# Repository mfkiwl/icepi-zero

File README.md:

# Icepi Zero - The portable FPGA development board. 

## What is the Icepi Zero?

Icepi Zero is an economical FPGA development board with a Raspberry Pi Zero form factor. It carries a Lattice ECP5 25F, enabling powerful designs while keeping a small portable size. It also has a HDMI port allowing easy digital video output.

[View PCB online](https://kicanvas.org/?github=https%3A%2F%2Fgithub.com%2Fcheyao%2Ficepi-zero%2Ftree%2Fmain%2Fhardware%2Fv1.1)

## Why Icepi Zero?

Currently most powerful FPGA boards on the market are expensive and bulky.

I've always wanted a low-cost portable FPGA with video output to make my own CPU, but there isn't any on the market.

The Icepi Zero aims to fix this. Carrying a powerful ECP5 FPGA on a small Raspberry Pi Zero form factor, it is the ultimate portable solution for FPGA development. Additionally packing a HDMI mini port and 3 USB-C ports, it allows interfacing with multiple external I/O devices.

Icepi Zero is for everyone: Students can use it to learn about the internals of modern processors. Gamers can use it to emulate old hardware. Programmers can use it to test their code on multiple architecturs.

Icepi Zero also has an on-board USB to JTAG converter, so no external programmers are needed. Moreover Icepi Zero is fully open-source, no strings attached. Fabricate your own boards if you want one!

## Features

- Raspberry Pi Zero form factor
- Lattice ECP5U FPGA:
    - 24k LUT
    - 112 KiB of RAM
- One MiniGPDI connector (it's HDM- but I don't have the money to buy a license...)
- Three USB-C Ports
- 256MiB 166MHz SDRAM
- MicroSD card slot
- On-board USB to JTAG and UART converter
- 40MHz external oscillator
- 128 Mbit of flash
- 4 user LEDs
- 1 user button

This powerful configuration allows the PCB to be used in numerous ways, including real time video processing, hardware AI acceleration and prototyping of ASICs.

## Usage

Check out the `firmware` folder for example code and compilation instructions!

## Contact

If there is any questions DM `@Cyao` on Hackclub Slack or `cyao.` on Discord. Mail is also accepted at `cyao _at_ duck.com`.

Thanks Hackclub for sponsering this! Check out [highway & undercity, a hackathon at Github HQ](https://highway.hackclub.com/?ref=recg6V5Pj0JbZghRM)

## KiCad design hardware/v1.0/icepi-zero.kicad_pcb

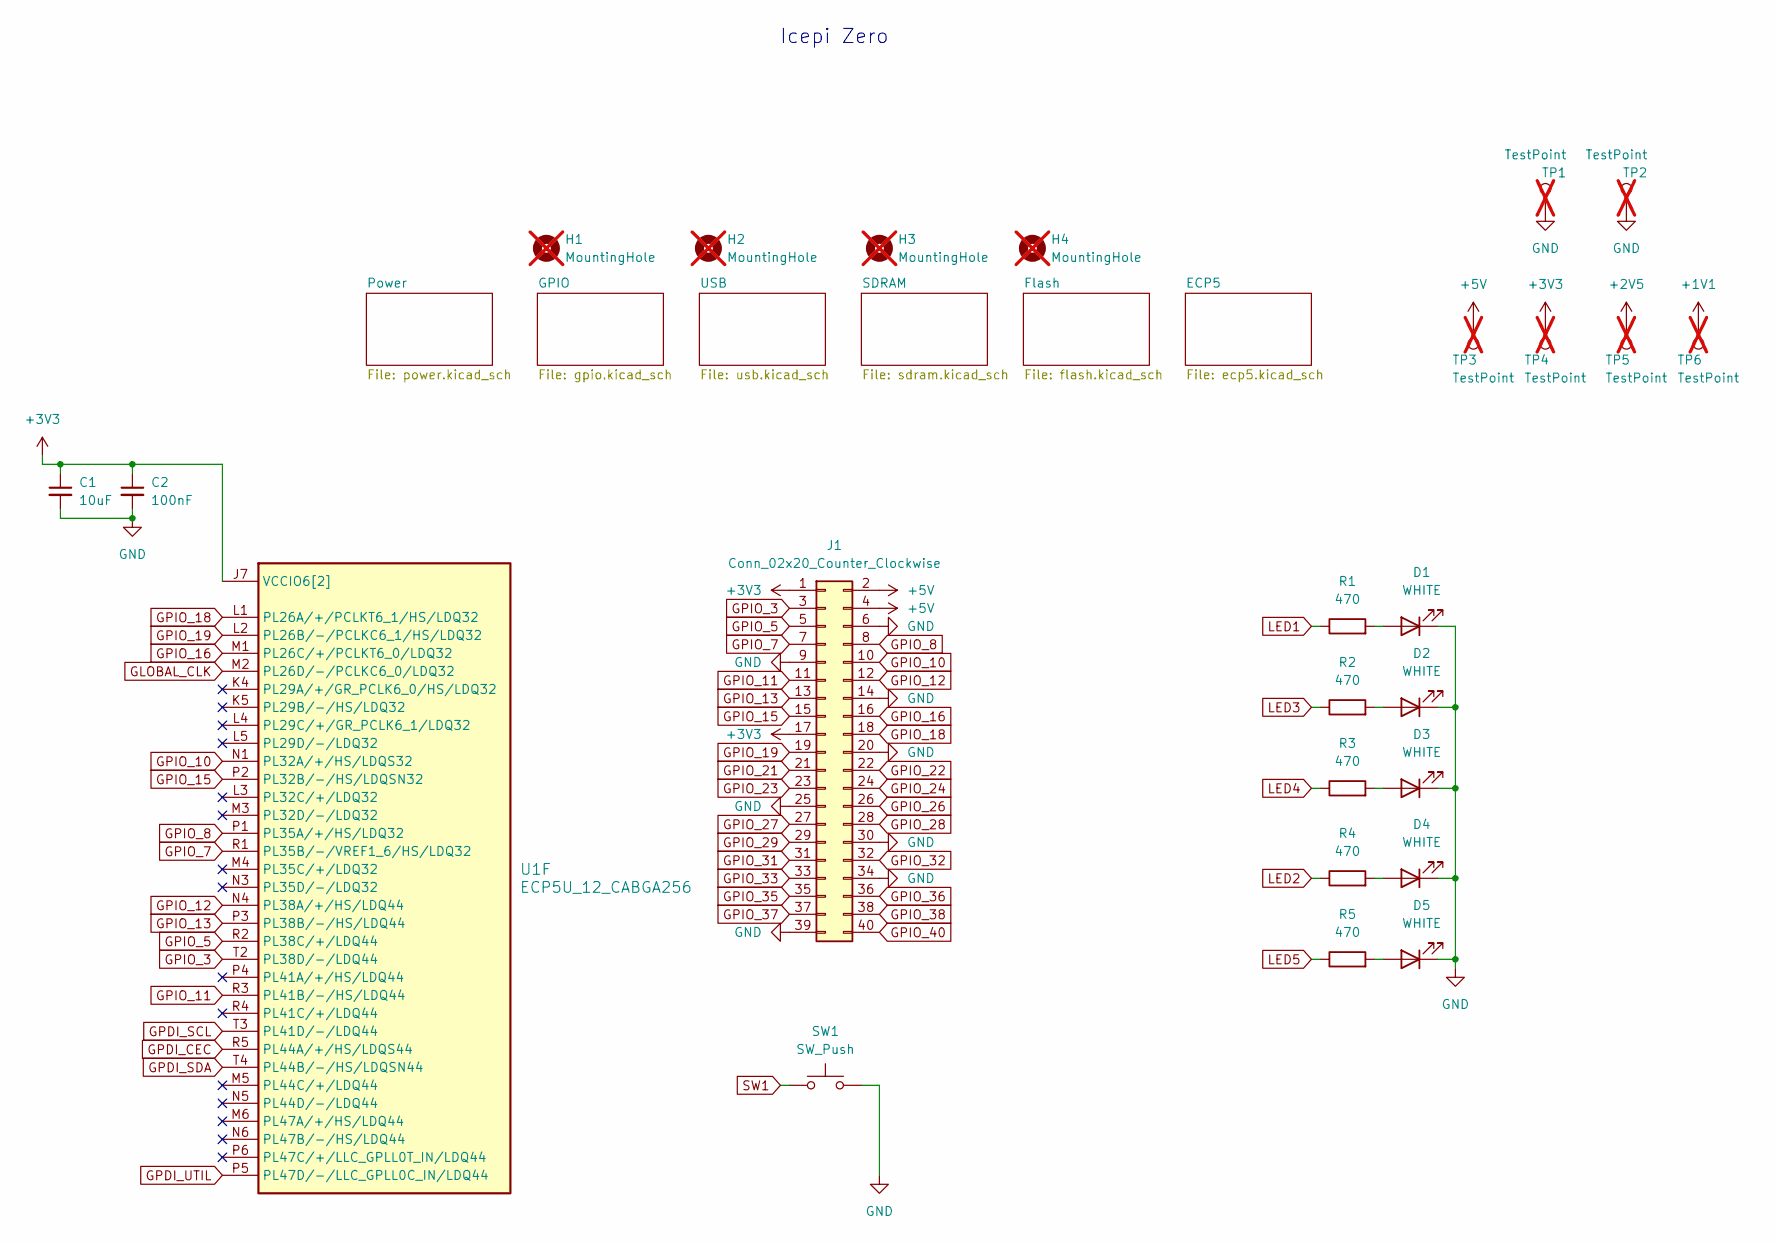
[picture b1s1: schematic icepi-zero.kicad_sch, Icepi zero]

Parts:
C1: 10uF; C_0603_1608Metric; LCSC Part # C19702
C2: 100nF; C_0402_1005Metric; LCSC Part # C307331
D1, D2, D3, D4, D5: WHITE; LED_0603_1608Metric; LCSC Part # C2290
H1, H2, H3, H4: MountingHole; MountingHole_2.7mm_M2.5; not fitted
J1: Conn_02x20_Counter_Clockwise; PinHeader_2x20_P2.54mm_Vertical
R1, R2, R3, R4, R5: 470; R_0402_1005Metric; LCSC Part # C25117
SW1: SW_Push; SW_SPST_B3U-1000P; LCSC Part # C2689695
TP1, TP2, TP3, TP4, TP5, TP6: TestPoint; TestPoint_Pad_D2.0mm; not fitted
U1: ECP5U_12_CABGA256; BGA-256_14.0x14.0mm_Layout16x16_P0.8mm_Ball0.45mm_Pad0.32mm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; LCSC Part # C1521614

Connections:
+1V1: TP6.1; also elsewhere on the board
+2V5: TP5.1; also elsewhere on the board
+3V3: C1.1, C2.1, J1.1, J1.17, TP4.1, U1.J6 (VCCIO6[2]), U1.J7 (VCCIO6[2]); also elsewhere on the board
+5V: J1.2, J1.4, TP3.1; also elsewhere on the board
GLOBAL_CLK: U1.M2 (PL26D/-/PCLKC6_0/LDQ32); also elsewhere on the board
GND: C1.2, C2.2, D1.1 (K), D2.1 (K), D3.1 (K), D4.1 (K), D5.1 (K), J1.6, J1.9, J1.14, J1.20, J1.25, J1.30, J1.34, J1.39, SW1.2, TP1.1, TP2.1; also elsewhere on the board
GPDI_CEC: U1.R5 (PL44A/+/HS/LDQS44); also elsewhere on the board
GPDI_SCL: U1.T3 (PL41D/-/LDQ44); also elsewhere on the board
GPDI_SDA: U1.T4 (PL44B/-/HS/LDQSN44); also elsewhere on the board
GPDI_UTIL: U1.P5 (PL47D/-/LLC_GPLL0C_IN/LDQ44); also elsewhere on the board
GPIO_3: J1.3, U1.T2 (PL38D/-/LDQ44)
GPIO_5: J1.5, U1.R2 (PL38C/+/LDQ44)
GPIO_7: J1.7, U1.R1 (PL35B/-/VREF1_6/HS/LDQ32)
GPIO_8: J1.8, U1.P1 (PL35A/+/HS/LDQ32)
GPIO_10: J1.10, U1.N1 (PL32A/+/HS/LDQS32)
GPIO_11: J1.11, U1.R3 (PL41B/-/HS/LDQ44)
GPIO_12: J1.12, U1.N4 (PL38A/+/HS/LDQ44)
GPIO_13: J1.13, U1.P3 (PL38B/-/HS/LDQ44)
GPIO_15: J1.15, U1.P2 (PL32B/-/HS/LDQSN32)
GPIO_16: J1.16, U1.M1 (PL26C/+/PCLKT6_0/LDQ32)
GPIO_18: J1.18, U1.L1 (PL26A/+/PCLKT6_1/HS/LDQ32)
GPIO_19: J1.19, U1.L2 (PL26B/-/PCLKC6_1/HS/LDQ32)
GPIO_21: J1.21; also elsewhere on the board
GPIO_22: J1.22; also elsewhere on the board
GPIO_23: J1.23; also elsewhere on the board
GPIO_24: J1.24; also elsewhere on the board
GPIO_26: J1.26; also elsewhere on the board
GPIO_27: J1.27; also elsewhere on the board
GPIO_28: J1.28; also elsewhere on the board
GPIO_29: J1.29; also elsewhere on the board
GPIO_31: J1.31; also elsewhere on the board
GPIO_32: J1.32; also elsewhere on the board
GPIO_33: J1.33; also elsewhere on the board
GPIO_35: J1.35; also elsewhere on the board
GPIO_36: J1.36; also elsewhere on the board
GPIO_37: J1.37; also elsewhere on the board
GPIO_38: J1.38; also elsewhere on the board
GPIO_40: J1.40; also elsewhere on the board
LED1: R1.1; also elsewhere on the board
LED2: R4.1; also elsewhere on the board
LED3: R2.1; also elsewhere on the board
LED4: R3.1; also elsewhere on the board
LED5: R5.1; also elsewhere on the board
unnamed: D1.2 (A), R1.2
unnamed: D2.2 (A), R2.2
unnamed: D3.2 (A), R3.2
unnamed: D4.2 (A), R4.2
unnamed: D5.2 (A), R5.2
SW1: SW1.1; also elsewhere on the board

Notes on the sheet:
Icepi Zero

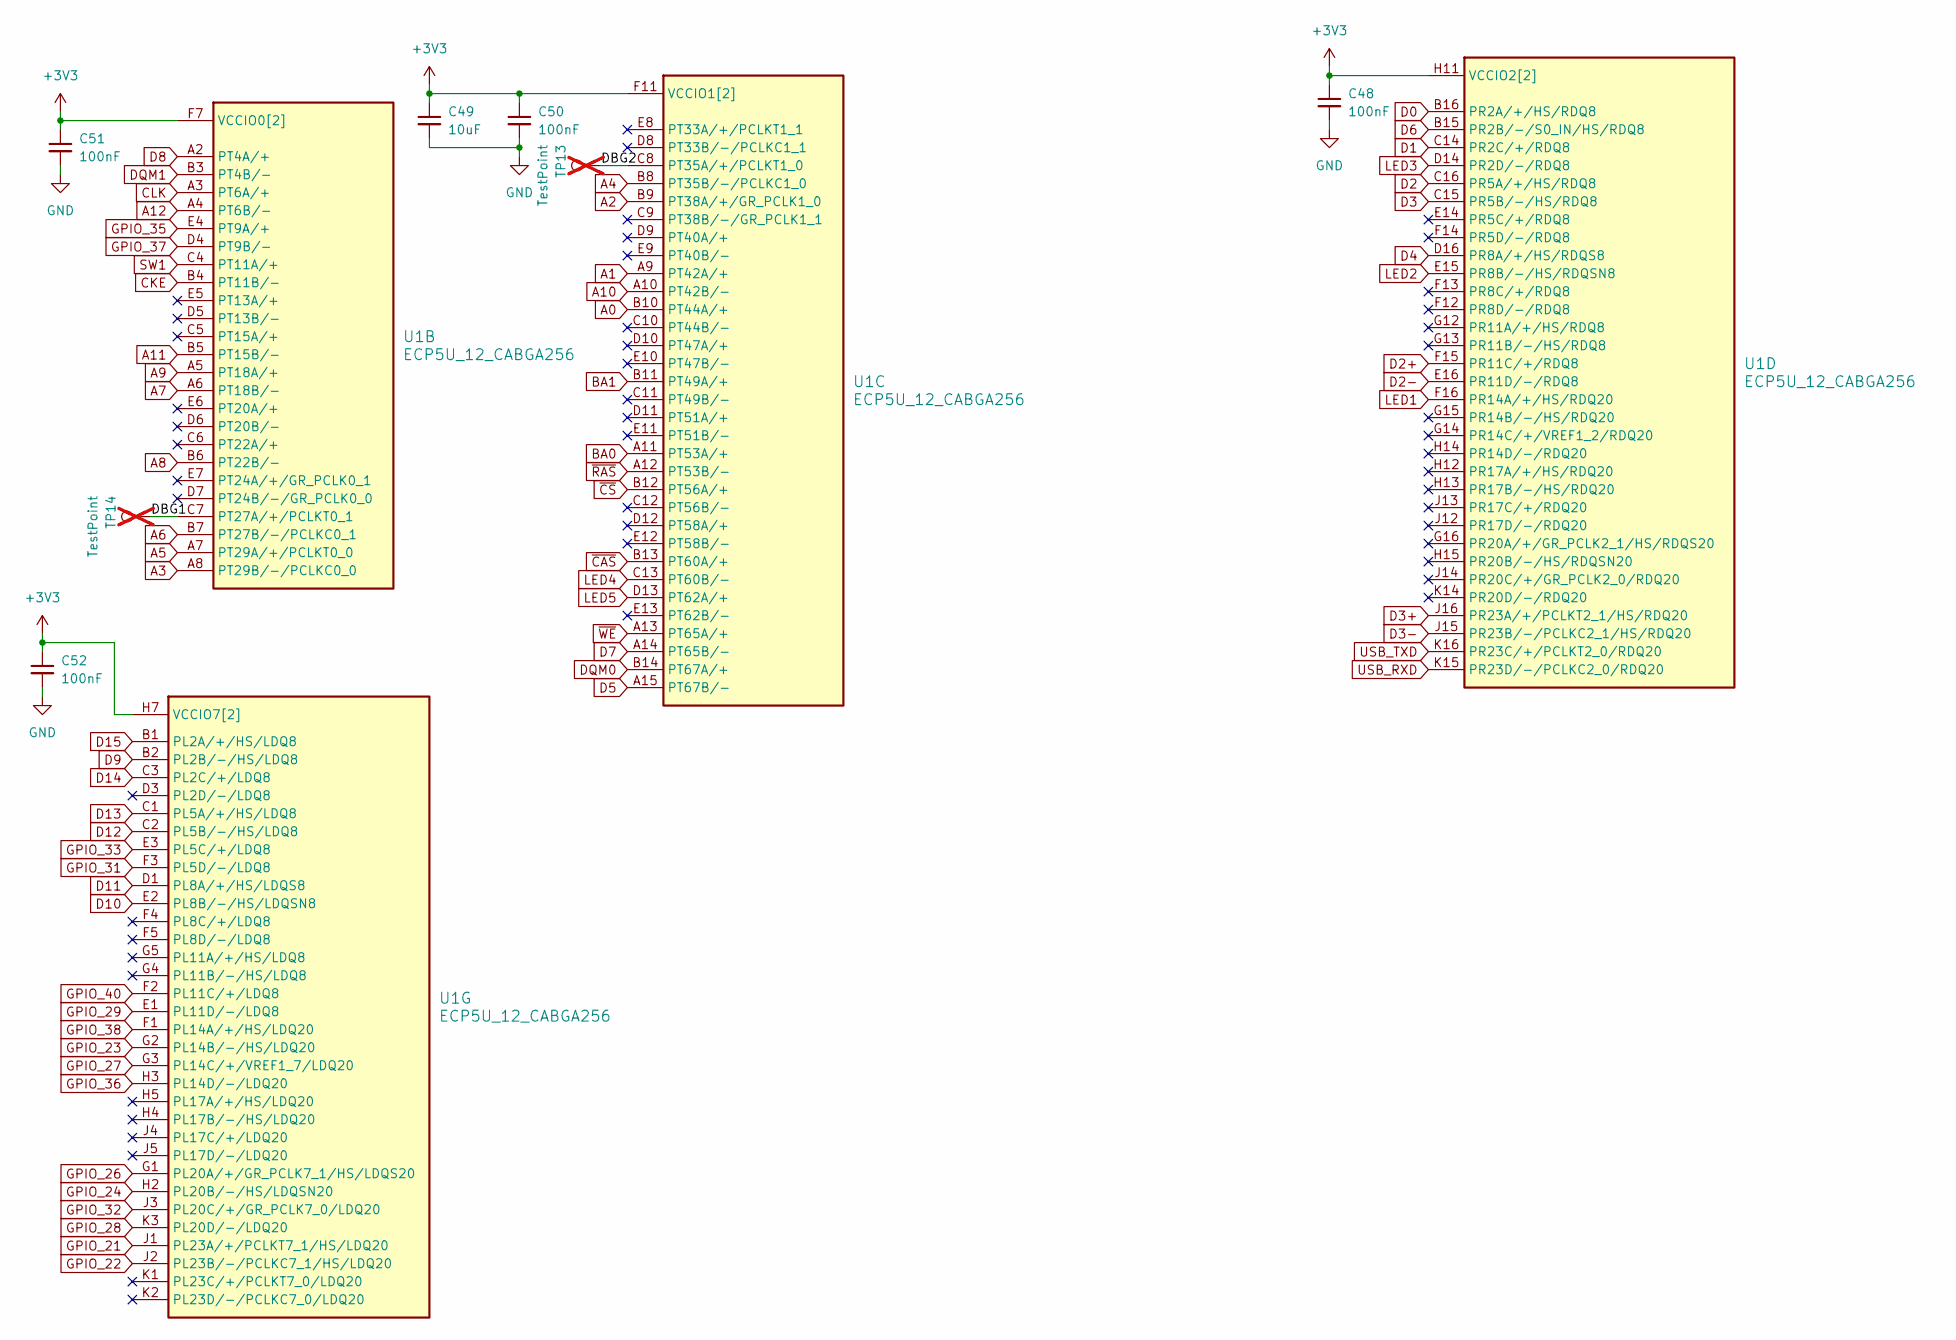
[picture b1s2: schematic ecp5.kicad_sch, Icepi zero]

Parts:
C48, C50, C51, C52: 100nF; C_0402_1005Metric; LCSC Part # C307331
C49: 10uF; C_0603_1608Metric; LCSC Part # C19702
TP13, TP14: TestPoint; TestPoint_Pad_D1.0mm; not fitted
U1: ECP5U_12_CABGA256; BGA-256_14.0x14.0mm_Layout16x16_P0.8mm_Ball0.45mm_Pad0.32mm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; LCSC Part # C1521614

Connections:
+3V3: C48.1, C49.1, C50.1, C51.1, C52.1, U1.F6 (VCCIO0[2]), U1.F7 (VCCIO0[2]), U1.F10 (VCCIO1[2]), U1.F11 (VCCIO1[2]), U1.H6 (VCCIO7[2]), U1.H7 (VCCIO7[2]), U1.H11 (VCCIO2[2]), U1.J11 (VCCIO2[2]); also elsewhere on the board
/ECP5/DBG1: TP14.1, U1.C7 (PT27A/+/PCLKT0_1)
/ECP5/DBG2: TP13.1, U1.C8 (PT35A/+/PCLKT1_0)
A0: U1.B10 (PT44A/+); also elsewhere on the board
A1: U1.A9 (PT42A/+); also elsewhere on the board
A2: U1.B9 (PT38A/+/GR_PCLK1_0); also elsewhere on the board
A3: U1.A8 (PT29B/-/PCLKC0_0); also elsewhere on the board
A4: U1.B8 (PT35B/-/PCLKC1_0); also elsewhere on the board
A5: U1.A7 (PT29A/+/PCLKT0_0); also elsewhere on the board
A6: U1.B7 (PT27B/-/PCLKC0_1); also elsewhere on the board
A7: U1.A6 (PT18B/-); also elsewhere on the board
A8: U1.B6 (PT22B/-); also elsewhere on the board
A9: U1.A5 (PT18A/+); also elsewhere on the board
A10: U1.A10 (PT42B/-); also elsewhere on the board
A11: U1.B5 (PT15B/-); also elsewhere on the board
A12: U1.A4 (PT6B/-); also elsewhere on the board
BA0: U1.A11 (PT53A/+); also elsewhere on the board
BA1: U1.B11 (PT49A/+); also elsewhere on the board
CKE: U1.B4 (PT11B/-); also elsewhere on the board
CLK: U1.A3 (PT6A/+); also elsewhere on the board
D0: U1.B16 (PR2A/+/HS/RDQ8); also elsewhere on the board
D1: U1.C14 (PR2C/+/RDQ8); also elsewhere on the board
D2: U1.C16 (PR5A/+/HS/RDQ8); also elsewhere on the board
D2+: U1.F15 (PR11C/+/RDQ8); also elsewhere on the board
D2-: U1.E16 (PR11D/-/RDQ8); also elsewhere on the board
D3: U1.C15 (PR5B/-/HS/RDQ8); also elsewhere on the board
D3+: U1.J16 (PR23A/+/PCLKT2_1/HS/RDQ20); also elsewhere on the board
D3-: U1.J15 (PR23B/-/PCLKC2_1/HS/RDQ20); also elsewhere on the board
D4: U1.D16 (PR8A/+/HS/RDQS8); also elsewhere on the board
D5: U1.A15 (PT67B/-); also elsewhere on the board
D6: U1.B15 (PR2B/-/S0_IN/HS/RDQ8); also elsewhere on the board
D7: U1.A14 (PT65B/-); also elsewhere on the board
D8: U1.A2 (PT4A/+); also elsewhere on the board
D9: U1.B2 (PL2B/-/HS/LDQ8); also elsewhere on the board
D10: U1.E2 (PL8B/-/HS/LDQSN8); also elsewhere on the board
D11: U1.D1 (PL8A/+/HS/LDQS8); also elsewhere on the board
D12: U1.C2 (PL5B/-/HS/LDQ8); also elsewhere on the board
D13: U1.C1 (PL5A/+/HS/LDQ8); also elsewhere on the board
D14: U1.C3 (PL2C/+/LDQ8); also elsewhere on the board
D15: U1.B1 (PL2A/+/HS/LDQ8); also elsewhere on the board
DQM0: U1.B14 (PT67A/+); also elsewhere on the board
DQM1: U1.B3 (PT4B/-); also elsewhere on the board
GND: C48.2, C49.2, C50.2, C51.2, C52.2; also elsewhere on the board
GPIO_21: U1.J1 (PL23A/+/PCLKT7_1/HS/LDQ20); also elsewhere on the board
GPIO_22: U1.J2 (PL23B/-/PCLKC7_1/HS/LDQ20); also elsewhere on the board
GPIO_23: U1.G2 (PL14B/-/HS/LDQ20); also elsewhere on the board
GPIO_24: U1.H2 (PL20B/-/HS/LDQSN20); also elsewhere on the board
GPIO_26: U1.G1 (PL20A/+/GR_PCLK7_1/HS/LDQS20); also elsewhere on the board
GPIO_27: U1.G3 (PL14C/+/VREF1_7/LDQ20); also elsewhere on the board
GPIO_28: U1.K3 (PL20D/-/LDQ20); also elsewhere on the board
GPIO_29: U1.E1 (PL11D/-/LDQ8); also elsewhere on the board
GPIO_31: U1.F3 (PL5D/-/LDQ8); also elsewhere on the board
GPIO_32: U1.J3 (PL20C/+/GR_PCLK7_0/LDQ20); also elsewhere on the board
GPIO_33: U1.E3 (PL5C/+/LDQ8); also elsewhere on the board
GPIO_35: U1.E4 (PT9A/+); also elsewhere on the board
GPIO_36: U1.H3 (PL14D/-/LDQ20); also elsewhere on the board
GPIO_37: U1.D4 (PT9B/-); also elsewhere on the board
GPIO_38: U1.F1 (PL14A/+/HS/LDQ20); also elsewhere on the board
GPIO_40: U1.F2 (PL11C/+/LDQ8); also elsewhere on the board
LED1: U1.F16 (PR14A/+/HS/RDQ20); also elsewhere on the board
LED2: U1.E15 (PR8B/-/HS/RDQSN8); also elsewhere on the board
LED3: U1.D14 (PR2D/-/RDQ8); also elsewhere on the board
LED4: U1.C13 (PT60B/-); also elsewhere on the board
LED5: U1.D13 (PT62A/+); also elsewhere on the board
SW1: U1.C4 (PT11A/+); also elsewhere on the board
USB_RXD: U1.K15 (PR23D/-/PCLKC2_0/RDQ20); also elsewhere on the board
USB_TXD: U1.K16 (PR23C/+/PCLKT2_0/RDQ20); also elsewhere on the board
~CAS: U1.B13 (PT60A/+); also elsewhere on the board
~CS: U1.B12 (PT56A/+); also elsewhere on the board
~RAS: U1.A12 (PT53B/-); also elsewhere on the board
~WE: U1.A13 (PT65A/+); also elsewhere on the board

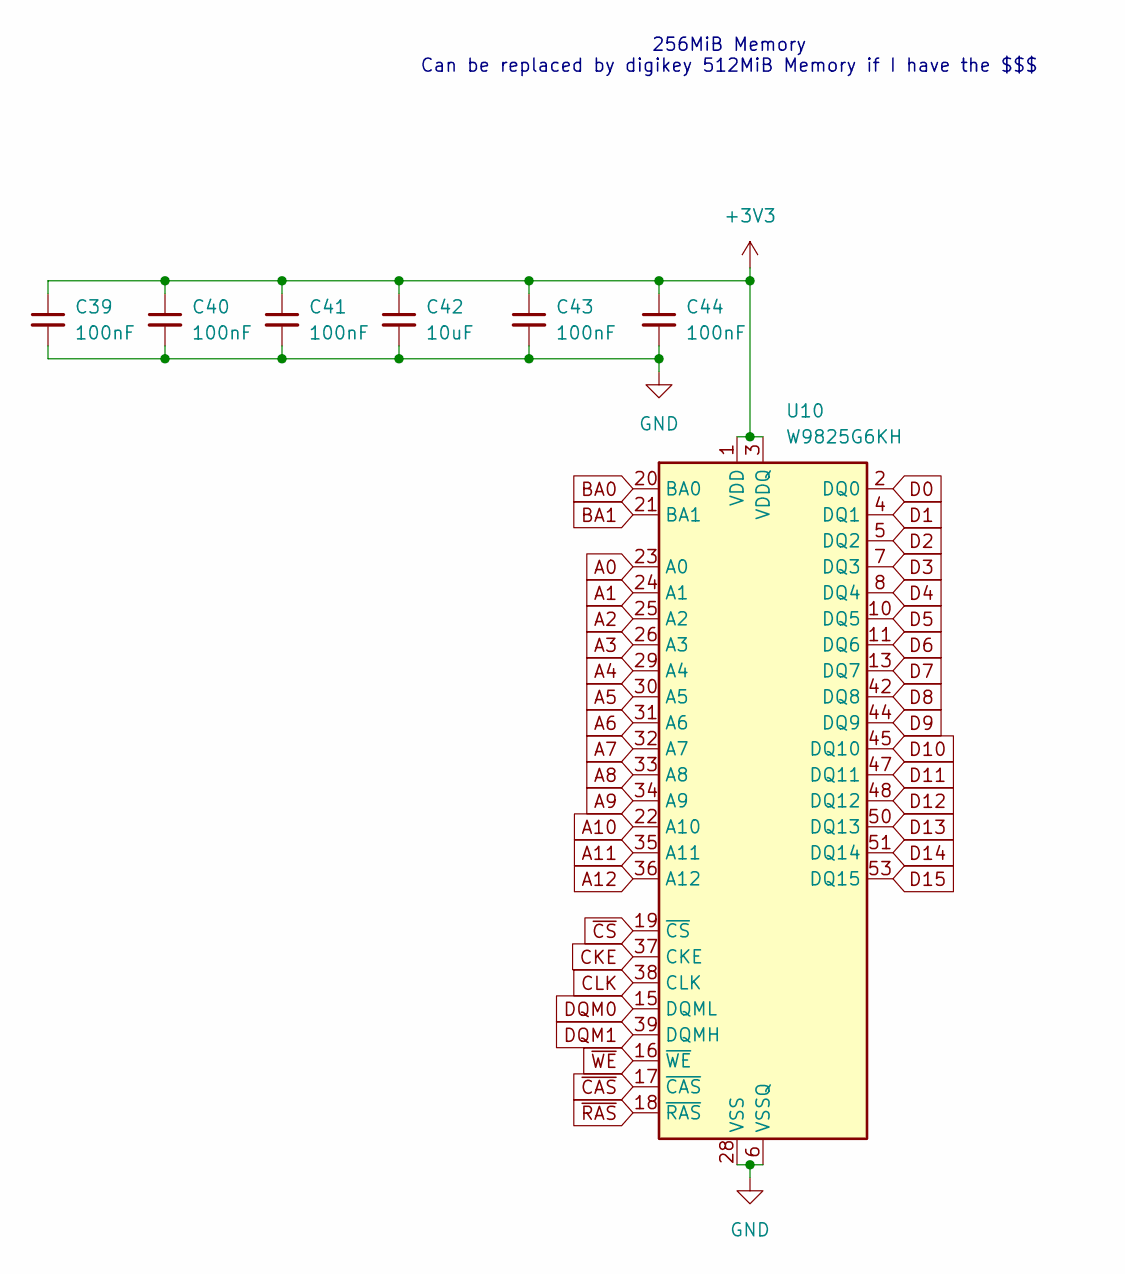
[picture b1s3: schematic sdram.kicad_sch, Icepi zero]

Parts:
C39, C40, C41, C43, C44: 100nF; C_0402_1005Metric; LCSC Part # C307331
C42: 10uF; C_0603_1608Metric; LCSC Part # C19702
U10: W9825G6KH; TSOP-II-54_22.2x10.16mm_P0.8mm; LCSC Part # C62246

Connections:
+3V3: C39.1, C40.1, C41.1, C42.1, C43.1, C44.1, U10.1 (VDD), U10.3 (VDDQ), U10.9 (VDDQ), U10.14 (VDD), U10.27 (VDD), U10.43 (VDDQ), U10.49 (VDDQ); also elsewhere on the board
A0: U10.23 (A0); also elsewhere on the board
A1: U10.24 (A1); also elsewhere on the board
A2: U10.25 (A2); also elsewhere on the board
A3: U10.26 (A3); also elsewhere on the board
A4: U10.29 (A4); also elsewhere on the board
A5: U10.30 (A5); also elsewhere on the board
A6: U10.31 (A6); also elsewhere on the board
A7: U10.32 (A7); also elsewhere on the board
A8: U10.33 (A8); also elsewhere on the board
A9: U10.34 (A9); also elsewhere on the board
A10: U10.22 (A10); also elsewhere on the board
A11: U10.35 (A11); also elsewhere on the board
A12: U10.36 (A12); also elsewhere on the board
BA0: U10.20 (BA0); also elsewhere on the board
BA1: U10.21 (BA1); also elsewhere on the board
CKE: U10.37 (CKE); also elsewhere on the board
CLK: U10.38 (CLK); also elsewhere on the board
D0: U10.2 (DQ0); also elsewhere on the board
D1: U10.4 (DQ1); also elsewhere on the board
D2: U10.5 (DQ2); also elsewhere on the board
D3: U10.7 (DQ3); also elsewhere on the board
D4: U10.8 (DQ4); also elsewhere on the board
D5: U10.10 (DQ5); also elsewhere on the board
D6: U10.11 (DQ6); also elsewhere on the board
D7: U10.13 (DQ7); also elsewhere on the board
D8: U10.42 (DQ8); also elsewhere on the board
D9: U10.44 (DQ9); also elsewhere on the board
D10: U10.45 (DQ10); also elsewhere on the board
D11: U10.47 (DQ11); also elsewhere on the board
D12: U10.48 (DQ12); also elsewhere on the board
D13: U10.50 (DQ13); also elsewhere on the board
D14: U10.51 (DQ14); also elsewhere on the board
D15: U10.53 (DQ15); also elsewhere on the board
DQM0: U10.15 (DQML); also elsewhere on the board
DQM1: U10.39 (DQMH); also elsewhere on the board
GND: C39.2, C40.2, C41.2, C42.2, C43.2, C44.2, U10.6 (VSSQ), U10.12 (VSSQ), U10.28 (VSS), U10.41 (VSS), U10.46 (VSSQ), U10.52 (VSSQ), U10.54 (VSS); also elsewhere on the board
~CAS: U10.17 (~CAS); also elsewhere on the board
~CS: U10.19 (~CS); also elsewhere on the board
~RAS: U10.18 (~RAS); also elsewhere on the board
~WE: U10.16 (~WE); also elsewhere on the board

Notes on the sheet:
256MiB Memory Can be replaced by digikey 512MiB Memory if I have the $$$

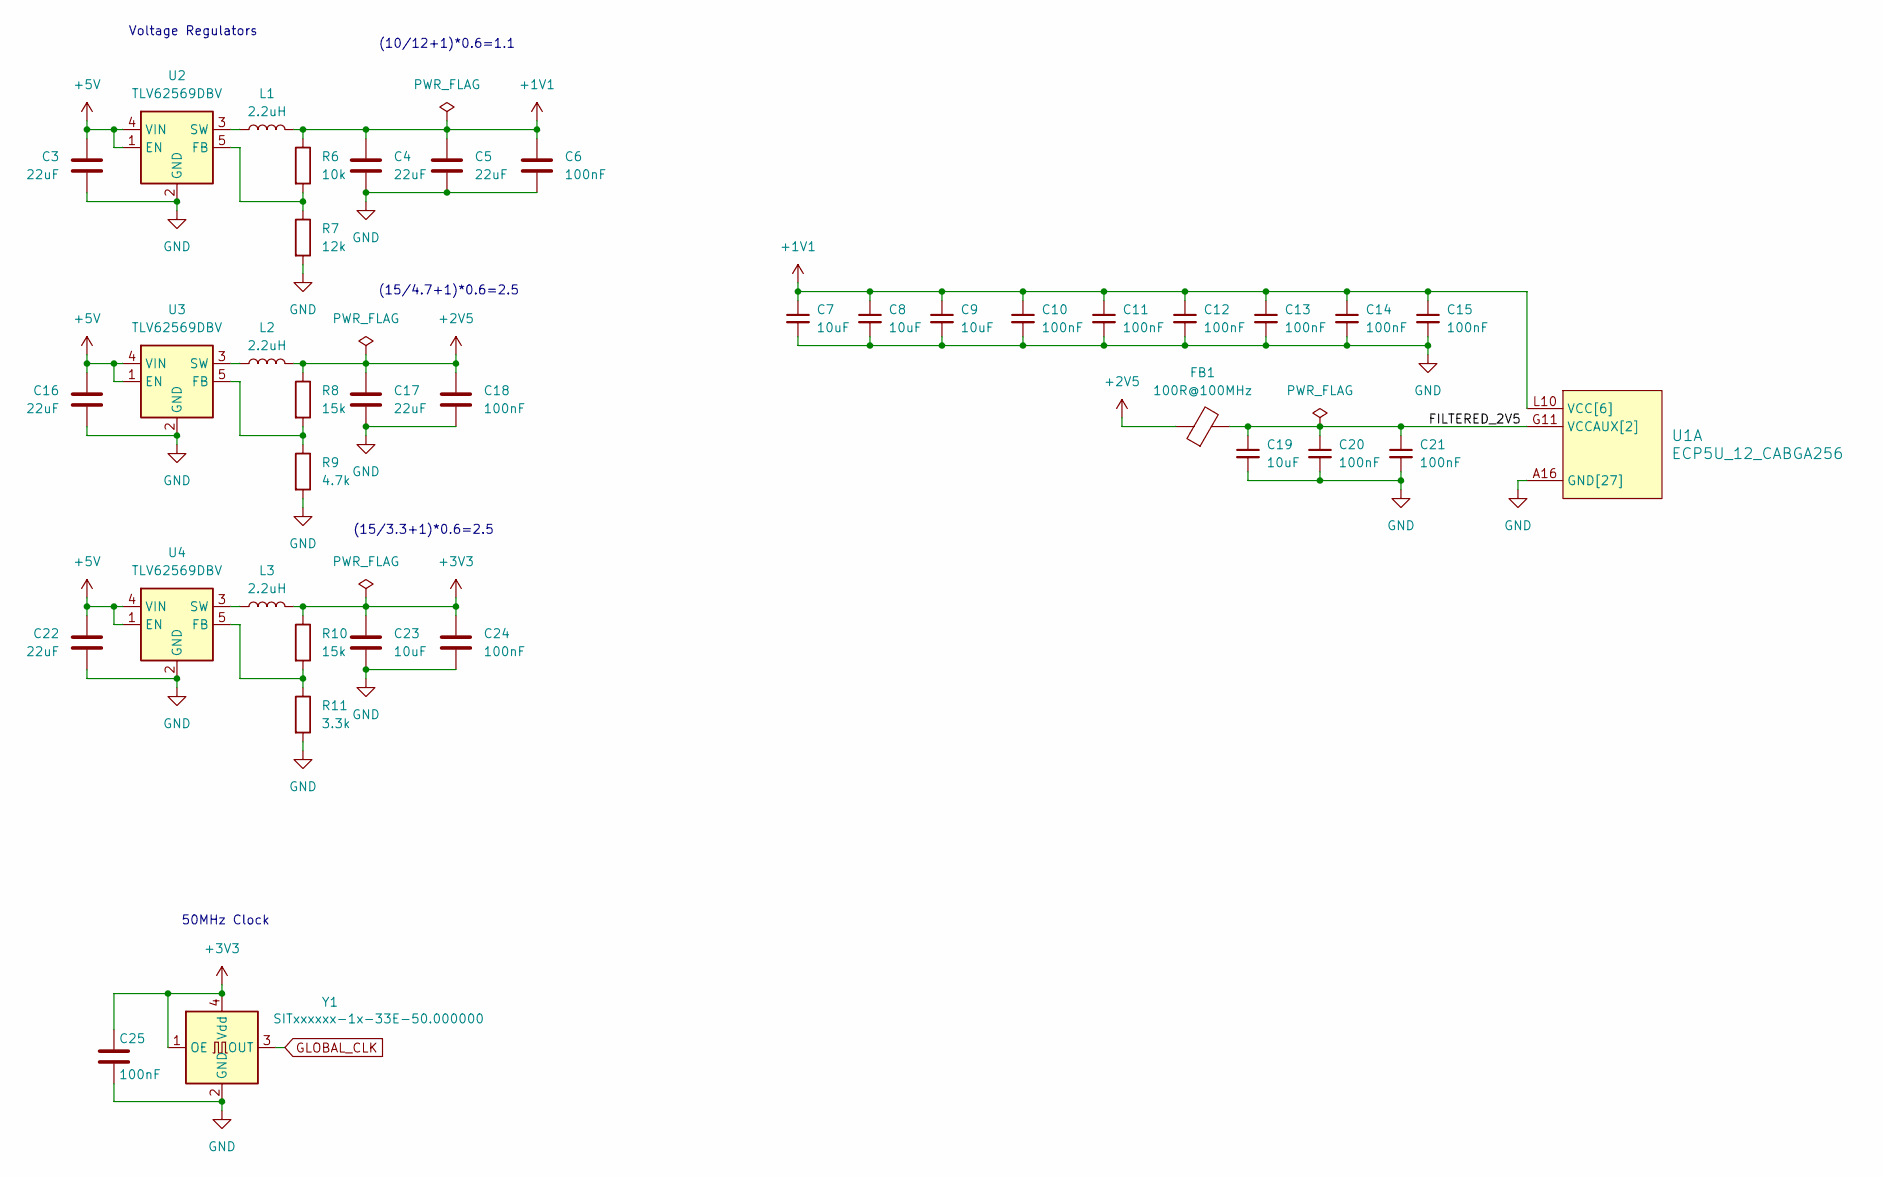
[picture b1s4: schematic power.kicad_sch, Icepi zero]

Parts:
C3, C4, C5, C16, C17, C22: 22uF; C_0603_1608Metric; LCSC Part # C59461
C6, C10, C11, C12, C13, C14, C15, C18, C20, C21, C24, C25: 100nF; C_0402_1005Metric; LCSC Part # C307331
C7, C8, C9, C19, C23: 10uF; C_0603_1608Metric; LCSC Part # C19702
FB1: 100R@100MHz; L_0805_2012Metric; LCSC Part # C1015
L1, L2, L3: 2.2uH; L_0805_2012Metric; LCSC Part # C1043
R6: 10k; R_0402_1005Metric; LCSC Part # C25744
R7: 12k; R_0402_1005Metric; LCSC Part # C25752
R8, R10: 15k; R_0402_1005Metric; LCSC Part # C25756
R9: 4.7k; R_0402_1005Metric; LCSC Part # C25900
R11: 3.3k; R_0402_1005Metric; LCSC Part # C25890
U1: ECP5U_12_CABGA256; BGA-256_14.0x14.0mm_Layout16x16_P0.8mm_Ball0.45mm_Pad0.32mm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; LCSC Part # C1521614
U2, U3, U4: TLV62569DBV; SOT-23-5; LCSC Part # C141836
Y1: SITxxxxxx-1x-33E-50.000000; Oscillator_SMD_SiT_PQFN-4Pin_2.5x2.0mm; LCSC Part # C1182928

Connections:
+1V1: C4.1, C5.1, C6.1, C7.1, C8.1, C9.1, C10.1, C11.1, C12.1, C13.1, C14.1, C15.1, L1.2, R6.1, U1.G6 (VCC[6]), U1.G7 (VCC[6]), U1.G9 (VCC[6]), U1.L8 (VCC[6]), U1.L9 (VCC[6]), U1.L10 (VCC[6]); also elsewhere on the board
+2V5: C17.1, C18.1, FB1.1, L2.2, R8.1; also elsewhere on the board
+3V3: C23.1, C24.1, C25.1, L3.2, R10.1, Y1.1 (OE), Y1.4 (Vdd); also elsewhere on the board
+5V: C3.1, C16.1, C22.1, U2.1 (EN), U2.4 (VIN), U3.1 (EN), U3.4 (VIN), U4.1 (EN), U4.4 (VIN); also elsewhere on the board
/Power/FILTERED_2V5: C19.1, C20.1, C21.1, FB1.2, U1.G11 (VCCAUX[2]), U1.L7 (VCCAUX[2])
GLOBAL_CLK: Y1.3 (OUT); also elsewhere on the board
GND: C3.2, C4.2, C5.2, C6.2, C7.2, C8.2, C9.2, C10.2, C11.2, C12.2, C13.2, C14.2, C15.2, C16.2, C17.2, C18.2, C19.2, C20.2, C21.2, C22.2, C23.2, C24.2, C25.2, R7.2, R9.2, R11.2, U1.A1 (GND[27]), U1.A16 (GND[27]), U1.D2 (GND[27]), U1.D15 (GND[27]), U1.F8 (GND[27]), U1.F9 (GND[27]), U1.G8 (GND[27]), U1.G10 (GND[27]), U1.H1 (GND[27]), U1.H8 (GND[27]), U1.H9 (GND[27]), U1.H10 (GND[27]), U1.H16 (GND[27]), U1.J8 (GND[27]), U1.J9 (GND[27]), U1.J10 (GND[27]), U1.K6 (GND[27]), U1.K7 (GND[27]), U1.K8 (GND[27]), U1.K9 (GND[27]), U1.K10 (GND[27]), U1.N2 (GND[27]), U1.N15 (GND[27]), U1.T1 (GND[27]), U1.T5 (GND[27]), U1.T12 (GND[27]), U1.T16 (GND[27]), U2.2 (GND), U3.2 (GND), U4.2 (GND), Y1.2 (GND); also elsewhere on the board
unnamed: R6.2, R7.1, U2.5 (FB)
unnamed: L1.1, U2.3 (SW)
unnamed: R8.2, R9.1, U3.5 (FB)
unnamed: L2.1, U3.3 (SW)
unnamed: R10.2, R11.1, U4.5 (FB)
unnamed: L3.1, U4.3 (SW)

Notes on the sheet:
(15/4.7+1)*0.6=2.5
(10/12+1)*0.6=1.1
(15/3.3+1)*0.6=2.5
50MHz Clock
Voltage Regulators

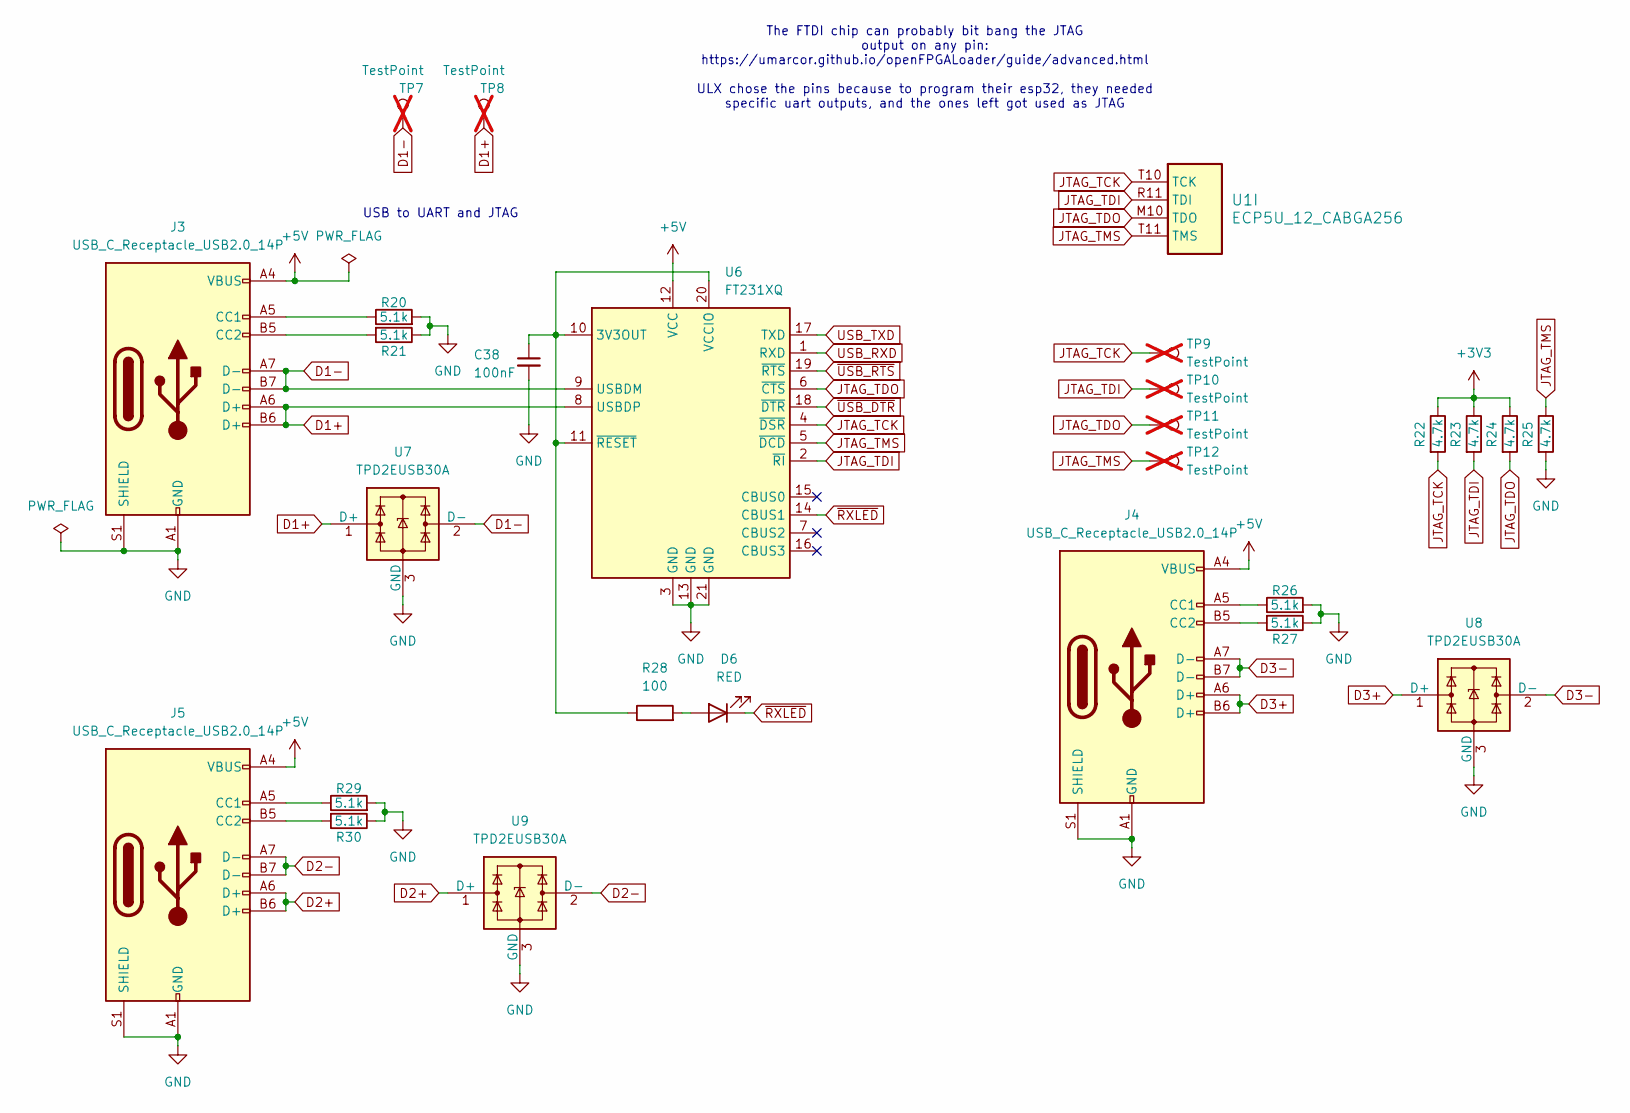
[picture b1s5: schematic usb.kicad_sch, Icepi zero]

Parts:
C38: 100nF; C_0402_1005Metric; LCSC Part # C307331
D6: RED; LED_0603_1608Metric; LCSC Part # C2286
J3, J4, J5: USB_C_Receptacle_USB2.0_14P; USB_C_Receptacle_GCT_USB4105-xx-A_16P_TopMnt_Horizontal; LCSC Part # C2765186
R20, R21, R26, R27, R29, R30: 5.1k; R_0402_1005Metric; LCSC Part # C25905
R22, R23, R24, R25: 4.7k; R_0402_1005Metric; LCSC Part # C25900
R28: 100; R_0402_1005Metric; LCSC Part # C25076
TP7, TP8: TestPoint; TestPoint_Pad_D2.0mm; not fitted
TP9, TP10, TP11, TP12: TestPoint; TestPoint_Pad_D1.0mm; not fitted
U1: ECP5U_12_CABGA256; BGA-256_14.0x14.0mm_Layout16x16_P0.8mm_Ball0.45mm_Pad0.32mm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; LCSC Part # C1521614
U6: FT231XQ; QFN-20-1EP_4x4mm_P0.5mm_EP2.5x2.5mm; LCSC Part # C132159
U7, U8, U9: TPD2EUSB30A; Texas_DRT-3; LCSC Part # C3011197

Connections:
+3V3: R22.1, R23.1, R24.1; also elsewhere on the board
+5V: J3.A4 (VBUS), J3.A9 (VBUS), J3.B4 (VBUS), J3.B9 (VBUS), J4.A4 (VBUS), J4.A9 (VBUS), J4.B4 (VBUS), J4.B9 (VBUS), J5.A4 (VBUS), J5.A9 (VBUS), J5.B4 (VBUS), J5.B9 (VBUS), U6.12 (VCC); also elsewhere on the board
D1+: J3.A6 (D+), J3.B6 (D+), TP8.1, U6.8 (USBDP), U7.1 (D+)
D1-: J3.A7 (D-), J3.B7 (D-), TP7.1, U6.9 (USBDM), U7.2 (D-)
D2+: J5.A6 (D+), J5.B6 (D+), U9.1 (D+); also elsewhere on the board
D2-: J5.A7 (D-), J5.B7 (D-), U9.2 (D-); also elsewhere on the board
D3+: J4.A6 (D+), J4.B6 (D+), U8.1 (D+); also elsewhere on the board
D3-: J4.A7 (D-), J4.B7 (D-), U8.2 (D-); also elsewhere on the board
GND: C38.2, J3.A1 (GND), J3.A12 (GND), J3.B1 (GND), J3.B12 (GND), J3.S1 (SHIELD), J4.A1 (GND), J4.A12 (GND), J4.B1 (GND), J4.B12 (GND), J4.S1 (SHIELD), J5.A1 (GND), J5.A12 (GND), J5.B1 (GND), J5.B12 (GND), J5.S1 (SHIELD), R20.2, R21.1, R25.2, R26.2, R27.1, R29.2, R30.1, U6.3 (GND), U6.13 (GND), U6.21 (GND), U7.3 (GND), U8.3 (GND), U9.3 (GND); also elsewhere on the board
JTAG_TCK: R22.2, TP9.1, U1.T10 (TCK), U6.4 (~DSR)
JTAG_TDI: R23.2, TP10.1, U1.R11 (TDI), U6.2 (~RI)
JTAG_TDO: R24.2, TP11.1, U1.M10 (TDO), U6.6 (~CTS)
JTAG_TMS: R25.1, TP12.1, U1.T11 (TMS), U6.5 (~DCD)
unnamed: D6.2 (A), R28.2
unnamed: J3.A5 (CC1), R20.1
unnamed: J3.B5 (CC2), R21.2
unnamed: J4.A5 (CC1), R26.1
unnamed: J4.B5 (CC2), R27.2
unnamed: J5.A5 (CC1), R29.1
unnamed: J5.B5 (CC2), R30.2
unnamed: C38.1, R28.1, U6.10 (3V3OUT), U6.11 (~RESET), U6.20 (VCCIO)
USB_RXD: U6.1 (RXD); also elsewhere on the board
USB_TXD: U6.17 (TXD); also elsewhere on the board
~RXLED: D6.1 (K), U6.14 (CBUS1)
~USB_DTR: U6.18 (~DTR); also elsewhere on the board
~USB_RTS: U6.19 (~RTS); also elsewhere on the board

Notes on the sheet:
USB to UART and JTAG
The FTDI chip can probably bit bang the JTAG output on any pin: https://umarcor.github.io/openFPGALoader/guide/advanced.html ULX chose the pins because to program their esp32, they needed specific uart outputs, and the ones left got used as JTAG

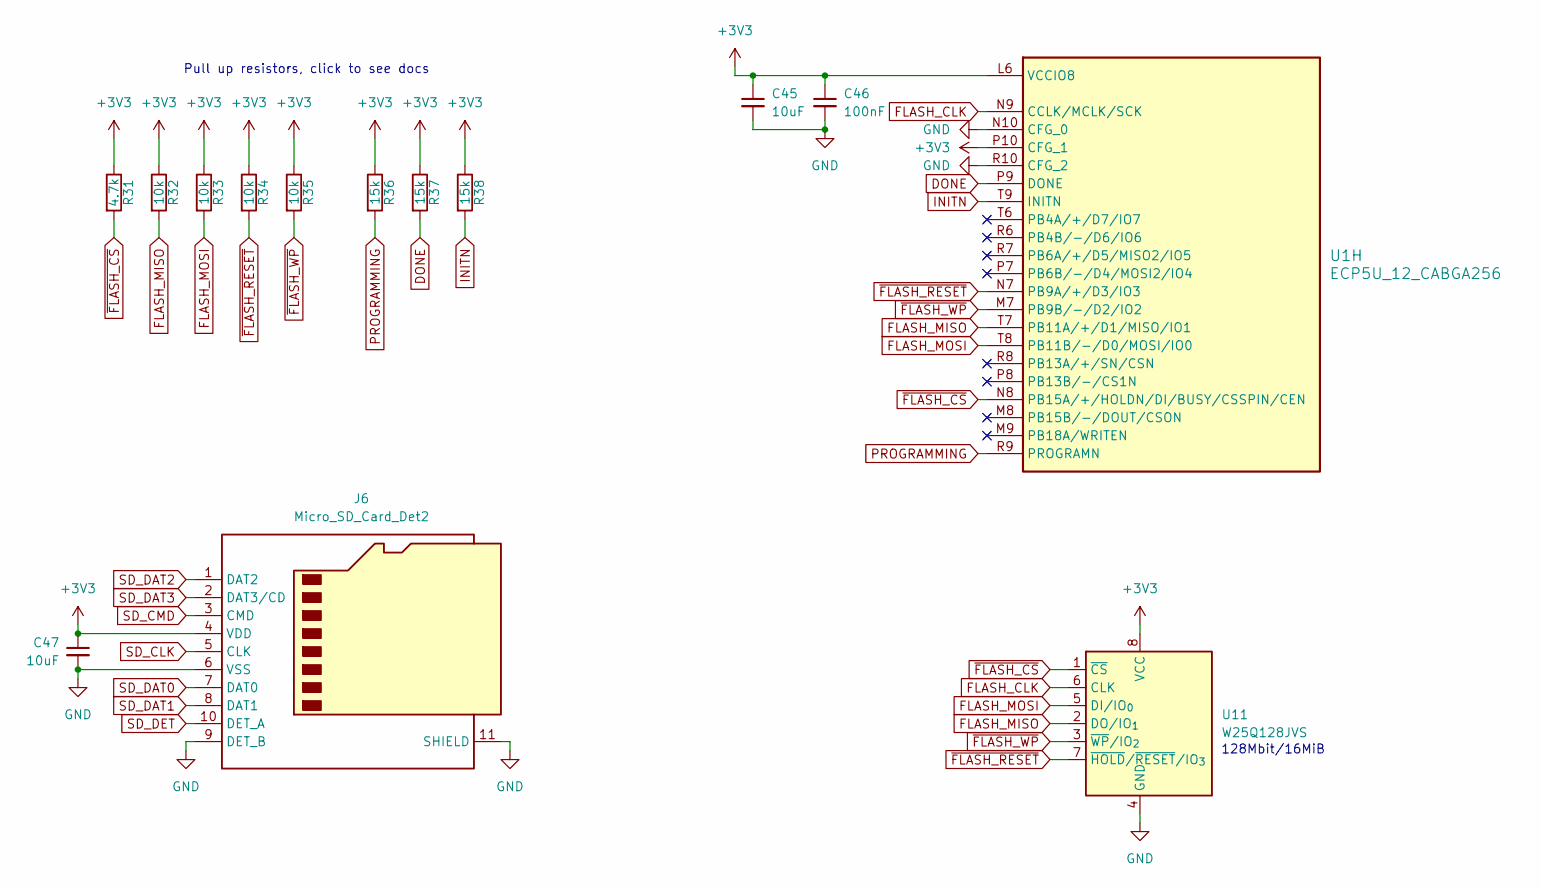
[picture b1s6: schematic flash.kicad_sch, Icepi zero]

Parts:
C45, C47: 10uF; C_0603_1608Metric; LCSC Part # C19702
C46: 100nF; C_0402_1005Metric; LCSC Part # C307331
J6: Micro_SD_Card_Det2; microSD_HC_SOFNG_TF-008; LCSC Part # C428465
R31: 4.7k; R_0402_1005Metric; LCSC Part # C25900
R32, R33, R34, R35: 10k; R_0402_1005Metric; LCSC Part # C25744
R36, R37, R38: 15k; R_0402_1005Metric; LCSC Part # C25756
U1: ECP5U_12_CABGA256; BGA-256_14.0x14.0mm_Layout16x16_P0.8mm_Ball0.45mm_Pad0.32mm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; LCSC Part # C1521614
U11: W25Q128JVS; SOIC-8_5.3x5.3mm_P1.27mm; LCSC Part # C97521

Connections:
+3V3: C45.1, C46.1, C47.1, J6.4 (VDD), R31.1, R32.1, R33.1, R34.1, R35.1, R36.1, R37.1, R38.1, U1.L6 (VCCIO8), U1.P10 (CFG_1), U11.8 (VCC); also elsewhere on the board
DONE: R37.2, U1.P9 (DONE)
FLASH_CLK: U1.N9 (CCLK/MCLK/SCK), U11.6 (CLK)
FLASH_MISO: R32.2, U1.T7 (PB11A/+/D1/MISO/IO1), U11.2 (DO/IO_{1})
FLASH_MOSI: R33.2, U1.T8 (PB11B/-/D0/MOSI/IO0), U11.5 (DI/IO_{0})
GND: C45.2, C46.2, C47.2, J6.6 (VSS), J6.9 (DET_B), J6.11 (SHIELD), U1.N10 (CFG_0), U1.R10 (CFG_2), U11.4 (GND); also elsewhere on the board
INITN: R38.2, U1.T9 (INITN)
PROGRAMMING: R36.2, U1.R9 (PROGRAMN)
SD_CLK: J6.5 (CLK); also elsewhere on the board
SD_CMD: J6.3 (CMD); also elsewhere on the board
SD_DAT0: J6.7 (DAT0); also elsewhere on the board
SD_DAT1: J6.8 (DAT1); also elsewhere on the board
SD_DAT2: J6.1 (DAT2); also elsewhere on the board
SD_DAT3: J6.2 (DAT3/CD); also elsewhere on the board
SD_DET: J6.10 (DET_A); also elsewhere on the board
~FLASH_CS: R31.2, U1.N8 (PB15A/+/HOLDN/DI/BUSY/CSSPIN/CEN), U11.1 (~CS)
~FLASH_RESET: R34.2, U1.N7 (PB9A/+/D3/IO3), U11.7 (~HOLD/~RESET/IO_{3})
~FLASH_WP: R35.2, U1.M7 (PB9B/-/D2/IO2), U11.3 (~WP/IO_{2})

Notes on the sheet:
128Mbit/16MiB
Pull up resistors, click to see docs
